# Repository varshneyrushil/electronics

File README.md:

# Electronics Hardware Portfolio

Hands-on electronics and systems work spanning **PCB design, embedded control, robotics, power electronics, wiring/harness integration, test engineering, and hardware prototyping**.

Most public material here comes from student engineering projects, Mars Rover Manipal, and university work from roughly 2019–2021. I have kept original source and project evidence where useful while adding context so that historical prototypes are not mistaken for current production designs.

> **Professional/confidential work is intentionally not published here.**

---

## Selected hardware

| Rover electronics & integration | STM32 / subsystem PCB design |
|---|---|
|  |  |
| System-level rover electronics integration, power distribution, wiring and subsystem packaging. | STM32-based rover subsystem/interface PCB developed to consolidate distributed interfaces and wiring. |

| Motor-driver interface | Indoor integration test mule |
|---|---|
|  |  |
| Recovered modular interface PCB carrying two motor-control signals plus ground between rover wiring and the motor-driver module. | Indoor Jetson/STM32 test platform used to test software, networking and video functionality without repeatedly deploying the full rover. |

| Battery characterization | Yagi-Uda antenna |
|---|---|
|  |  |
| Constant-current discharge testing used to obtain experimental battery voltage-vs-time behaviour. | Student-built directional antenna prototype based on Yagi-Uda element-spacing and length calculations. |

---

## Browse the actual source

### Mars Rover Manipal

- [STM32 subsystem/interface PCB](projects/mars-rover-manipal/stm32-subsystem-interface/)
- [Modular motor-driver interface](projects/mars-rover-manipal/motor-driver-interface/)
- [Robotic-arm 3-pin breakout](projects/mars-rover-manipal/robotic-arm-interface-3pin/)
- [Robotic-arm interface archive](projects/mars-rover-manipal/robotic-arm-interface/)
- [Camera interface archive](projects/mars-rover-manipal/camera-interface/)
- [Left-motor interface archive](projects/mars-rover-manipal/left-motor-interface/)
- [Right-motor interface archive](projects/mars-rover-manipal/right-motor-interface/)

### Other electronics projects

- [Discrete BJT H-bridge motor driver](projects/personal/discrete-motor-driver/)
- [ATmega16 breakout](projects/personal/atmega16-breakout/)
- [Optocoupler/interface board](projects/personal/optocoupler-interface/)
- [Reverse-polarity protection](projects/personal/reverse-polarity-protection/)

See the [project index](projects/) for source-format and provenance notes.

---

## Rover electronics & system integration

My Mars Rover Manipal work included electronics design and maintenance across:

- custom PCBs and subsystem interfaces;
- STM32-based control hardware;
- Jetson/MCU integration;
- power distribution and high-current wiring;
- embedded/data interfaces;
- motor-controller integration;
- harness fabrication and connector selection;
- electronics-box integration and troubleshooting;
- test fixtures and an indoor subsystem test mule.

The rover was a multidisciplinary team project. Images of the complete rover/electronics box represent the team system; the project READMEs describe the electronics work and surviving source rather than claiming sole authorship of the full machine.

---

## Motor control & prototyping

Early electronics work included transistor-level motor-control design and build iterations:

- discrete BJT H-bridge simulations;
- breadboard prototypes;
- hand-built perfboard implementations and rework;
- joystick-based differential-drive experiments;
- instrumented Proteus simulation;
- PCB/manufacturing outputs.

The [discrete motor-driver project](projects/personal/discrete-motor-driver/) includes an explicit authorship note because the surviving schematic was drawn within a shared student project.

---

## Battery test hardware & analogue instrumentation

I built an adjustable electronic load originally to characterize battery discharge behaviour. Surviving material documents:

- a low-resistance current shunt;
- separate voltage-sense wiring across the shunt;
- analogue gain calibration;
- an adjustable power stage;
- logged battery voltage measurements;
- the resulting voltage-vs-time discharge curve.

The exact final circuit revision no longer survives, so repository descriptions intentionally separate documented evidence from later reconstruction.

---

## Wiring, harnesses & repair

Rover integration also involved practical electrical assembly:

- high-current battery wiring;
- ferrule and connector crimping;
- Anderson-style power contacts;
- soldered XT-series connectors;
- ribbon/FRC wiring;
- Ethernet/LAN termination;
- screw-terminal and Wago-style connections;
- wire repair and field rework.

See [`images/harness/`](images/harness/) and the public job-instruction reports.

---

## Reports and documentation

[`reports_public/`](reports_public/) contains historical reports and engineering notes that I can share publicly, including:

- electronics/motor/battery training reports;
- antenna comparison and Yagi-Uda work;
- communication-protocol and embedded-C exercises;
- connector/fuseholder/battery-monitoring notes;
- wire-repair and battery-charging job instructions;
- a discrete motor-driver academic project;
- an HVDC research report.

These are retained primarily as **evidence of the engineering work and learning process at the time**, not as current design standards.

Larger team reports, internship documents and professional employer material are deliberately not included in this public-ready repository unless publication rights are clear.

---

## Context and provenance

For file-by-file context:

- [`CAPTIONS.md`](CAPTIONS.md)
- [`IMAGE_INDEX.csv`](IMAGE_INDEX.csv)
- [`REPORT_INDEX.csv`](REPORT_INDEX.csv)
- [`SOURCE_MAP.md`](SOURCE_MAP.md)
- [`NOTICE.md`](NOTICE.md)

---

## Main engineering areas represented

`Electronics` · `PCB Design` · `Embedded Systems` · `Motor Control` · `Power Electronics` · `Hardware Test` · `Harnessing & Interconnects` · `Robotics` · `MATLAB/Simulink` · `Proteus`

---

## About me

I am an electronics / systems engineer currently completing an MSc in Systems & Control at TU Delft. My professional experience includes regulated medical-device electronics and hardware verification, alongside power-electronics failure analysis and hands-on electronics development.

This repository focuses on public project material rather than confidential professional work.

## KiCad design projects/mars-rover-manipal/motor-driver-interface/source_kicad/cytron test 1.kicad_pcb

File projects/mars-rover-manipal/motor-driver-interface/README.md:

# Modular motor-driver interface PCB

Historical Mars Rover Manipal motor-driver interface.

## Confirmed from the surviving design

The KiCad source contains:

- a motor-driver module footprint;
- a 10-position rover-side connector;
- two 3-pin headers;
- two control nets plus ground.

The control nets are consistent with the PWM + direction interface of the Cytron motor-driver hardware used on the rover. Both 3-pin headers carry the same two control signals and ground, making this surviving revision a compact modular signal-routing/interface board.

An I²C-addressed architecture is **not** claimed for this particular source set because the recovered netlist does not show it.

## Included source

- `source_kicad/` — recovered/converted KiCad project
- `source_altium_legacy/cytron_test_1/` — earlier Altium project snapshot
- `source_altium_legacy/cytron_partial/` — another partial historical Altium snapshot
- `media/` — recovered layout image

Third-party connector library files found in the old archives are omitted from the public-ready package; see `THIRD_PARTY_LIBRARY_NOTICE.md`.

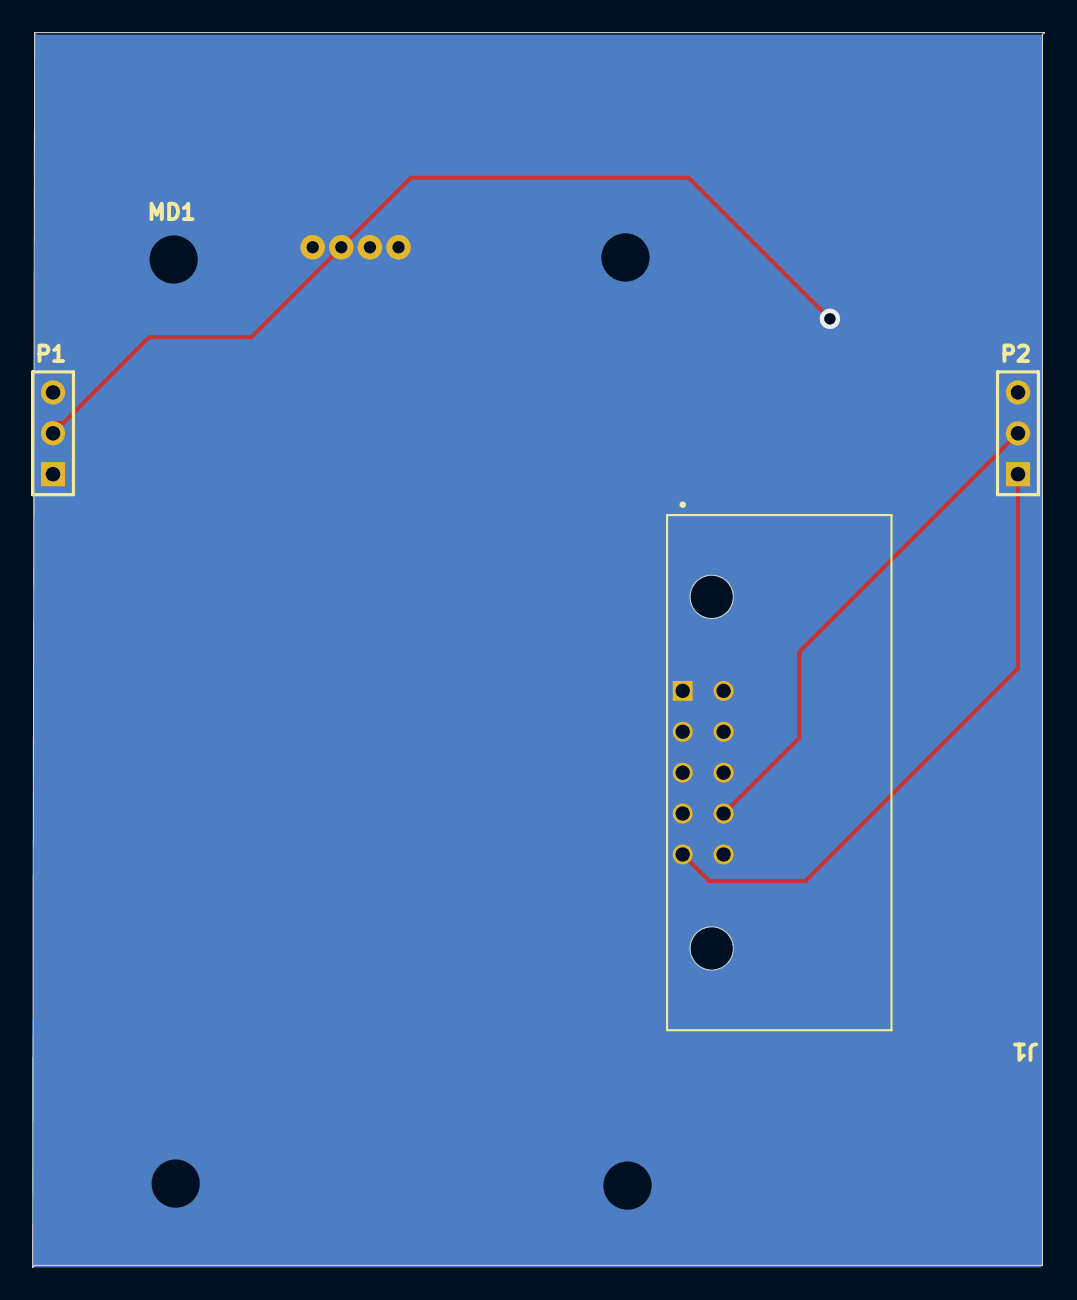
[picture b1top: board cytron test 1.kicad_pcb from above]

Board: 2 copper layers, 62.9 x 76.7 mm, 4 parts (0 on the bottom side), 3 nets.

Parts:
J1: 5499913-1; *TE_5499913-1
MD1: Component_1; PCBComponent_1
P1, P2: Header 3; HDR1X3

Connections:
GND: J1.1, MD1.4, P1.3, P2.3
NetJ1_8: J1.8, MD1.2, P1.2, P2.2
NetJ1_9: J1.9, MD1.1, P1.1, P2.1
